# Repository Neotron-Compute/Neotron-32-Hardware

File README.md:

# Neotron 32

## A simple 32K ARM-powered home computer.

The Neotron 32 brings the classic 1980s home-computer design up-to-date. Our tech is based on the tried and true single board ARM computer model offering a hacker friendly platform for your retro project. It aims to bring the retro computing feel, with DOS and BASIC like environments and semi-modern interfaces, like SD cards and SVGA. And all the system software is Open Source and written in the Rust Programming Language, and all the hardware is Open Source too.

With an ARM Cortex-M4 based MCU the Neotron-32 gets you right back into the hardware. With only 32 KiB of RAM, the challenge is to squeeze the maximum out of the minimum amount of resources. We've got 48x36 text mode, 384x288 bitmap mode, 3-channel audio synthesiser, joystick support and FAT filesystem support ... but there's still room for you to squeeze some more out the system.

## Hardware

  - **CPU:** Texas Instruments Tiva-C TM4C123
  - **Processor Core**: 80 MHz ARM Cortex-M4 (approximately 95% CPU taken drawing the screen, leaving a ~ 4 MHz ARM)
  - **RAM:** 32 KiB on-chip SRAM
  - **ROM:** 256 KiB on-chip Flash
  - **GPU:** No GPU - CPU generates 8 colour 400x300 video
  - **GPU RAM:** Shared with main SRAM
  - **Video Output:** VGA (fixed at 800x600 60 Hz)
  - **Storage:** Micro SD Card slot, supports FAT16/FAT32 and MS-DOS partition tables
  - **USB:** 1x USB 2.0 Full-speed OTG micro-AB port (internal - support TBD)
  - **Audio:** 3.5mm Line Out with Mono/Stereo jumper
  - **Keyboard/Mouse:** 2x PS/2 Ports (2x 6-pin mini-DIN)
  - **MIDI**: MIDI In and MIDI Out (2x 5-pin 180-degree DIN)
  - **Serial**: RS-232 on 10-pin 2.54mm header suitable for DE-9 plug on IDC ribbon
  - **Parallel**: 3.3v PC-style Parallel Port on 26-pin 2.54mm header suitable for DB-25 plug on IDC ribbon. Also functions as 3.3v GPIO with 12 outputs and 4 inputs.
  - **Joystick**: 2x 9-pin game ports (supports Atari-compatible two-button joysticks, or SEGA MegaDrive/Genesis controllers)
  - **Expansion**: 2x internal 2.54mm 2x6 headers carrying power, SPI, I2C and a dedicated IRQ line
  - **Wi-Fi**: 2x4 pin socket for ESP-01 Wi-Fi module
  - **RTC**: MCP7940 Real-time clock, with coin-cell battery backup
  - **Mechanical Form Factor:** Fits Hammond [1598C] case

[1598C]: ./datasheets/Hammond%201598C.pdf

## Parts Required

  - **PCBA**: Load the [Neotron-32 schematic](./neotron-32.sch) in Kicad, or see the [Neotron-32 Release Area] on Github for PDFs, Gerbers and a CSV bill-of-materials.
  - **Case**: Hammond [1598C], in your choice of colour. The case will include mounting screws, feet and two un-cut end panels.
  - **End panels**: Cut the panels supplied with the case according to [the drawing](./endpanels/endpanels.dxf). There is a PDF version in the [Neotron-32 Release Area].
  - **SD Card**: Any micro-SD or micro-SDHC card should work. Tested with Sandisk 8GB micro-SDHC cards, formatted with a single FAT32 partition.
  - **Monitor**: You will need monitor with 15-pin VGA input that can handle 800x600 resolution @ 60 Hz. Most higher resolution LCD panels will up-scale the image, but the quality of the scaling may not be ideal. A CRT will give a better image, but you may need to wind up the contrast and brightness to get a workable picture. An old 800x600 native resolution LCD would be ideal.
  - **Power Supply**: You need a standard mobile phone charger or other USB power source, and a standard USB A to B cable (like you would use for a USB printer).
  - **Ribbon cables**: The DB25 Parallel Port and DE9 RS-232 Serial port require a 2.54mm pin header to D-Sub ribbon cable. You can scavenge them from an old PC, or buy them new from Amazon, eBay or AliExpress for a few UK pounds.
  - **Keyboard and Mouse**: Any PS/2 Keyboard and PS/2 Mouse should work. In theory you could also use an RS-232 Serial Mouse but there's no driver support for that.
  - **Tiva-C Launchpad**: Contains the brains of the system. You want the EK-TM4C123GXL - *not* the EK-TM4C129 (which is much larger), or the older LM4F120 Launchpad (which is almost compatible, but audio won't work). You can buy these online at places like [Digikey](https://www.digikey.co.uk/products/en?keywords=296-35760-ND) or [Farnell](https://uk.farnell.com/texas-instruments/ek-tm4c123gxl/launchpad-tiva-c-evaluation-kit/dp/3126091).
  - **Joysticks**: Any Atari-compatible 9-pin digital joystick should work. You can connect up to two at once, for two player gaming. Sega MegaDrive/Genesis controllers should also work (although on the 6-button variant only the main A/B/C/Start buttons will work, not the extra three fire buttons).
  - **Audio**: The audio output is straight from the microcontroller and so is pretty weak. We recommend using amplified speakers, or an external headphone amplifier. Connecting headphones directly is untested and may pull too much current from the microcontroller.
  - **MIDI**: If you want to hook up a MIDI Synthesiser like a Roland MT-32, or a MIDI Keyboard, you just need standard 5-pin DIN MIDI cables. USB MIDI devices are not supported.
  - **USB**: The Tiva-C Launchpad has a USB micro-AB connector into which you can plug a Raspberry Pi Zero compatible micro-A to full-size A adaptor. There is no USB support in firmware yet, and the board can only supply a limited amount of current, so don't expect your mobile phone to charge.
  - **Switches**: You'll need a 250 mA On/Off switch you can fix to the case to power the unit on (or short the header with a jumper), plus a momentary switch to reset the system.

You can find a complete BOM (including the Tiva-C Launchpad and all the connectors, but excluding the PCB, case and Serial/Parallel ribbon cables), on [Octopart]. Gerbers and BOM are also available on [OpenHardware] and [Kitspace]. Don't forget, if you get the Hammond case, you'll need to drill out or mill the endplates yourself to take the connectors.

[Neotron-32 Release Area]: https://github.com/Neotron-Compute/Neotron-32-Hardware/releases
[Octopart]: https://octopart.com/bom-tool/tBdBR3vl
[OpenHardware]: https://www.openhardware.io/view/783/Neotron-32
[Kitspace]: https://kitspace.org/boards/github.com/neotron-compute/neotron-32-hardware/

## Git Setup

We recommend you have the following Git config set:

```console
$ git config --global filter.kicad_project.clean "sed -E 's/^update=.*$/update=Date/'"
$ git config --global filter.kicad_project.smudge cat
$ git config --global filter.kicad_sch.clean "sed -E 's/#(PWR|FLG)[0-9]+/#\1?/'"
$ git config --global filter.kicad_sch.smudge cat
```

See https://jnavila.github.io/plotkicadsch/ for details.

## Software

You will need to flash both the [Neotron 32 BIOS](https://github.com/neotron-compute/Neotron-32-BIOS) and the [Neotron OS](https://github.com/neotron-compute/Neotron-OS). The TM4C123 Launchpad has an on-board USB programming tool, which is supported by OpenOCD, so no extra hardware is required.

Once running the OS, you can load applications from the SD card. Applications can be written in C or in Rust, using the [Neotron SDK](https://github.com/neotron-compute/Neotron-SDK).

## Licence

This schematic and PCB design is Copyright (c) Jonathan 'theJPster' Pallant and other Neotron 32 contributors.

This work is licensed under a [Creative Commons Attribution-ShareAlike 4.0 International License](http://creativecommons.org/licenses/by-sa/4.0/).

## Contribution Agreement

Unless you explicitly state otherwise, any contribution intentionally submitted for inclusion in the work by you, as defined in the Apache-2.0 license, shall be licensed as above, without any additional terms or conditions.

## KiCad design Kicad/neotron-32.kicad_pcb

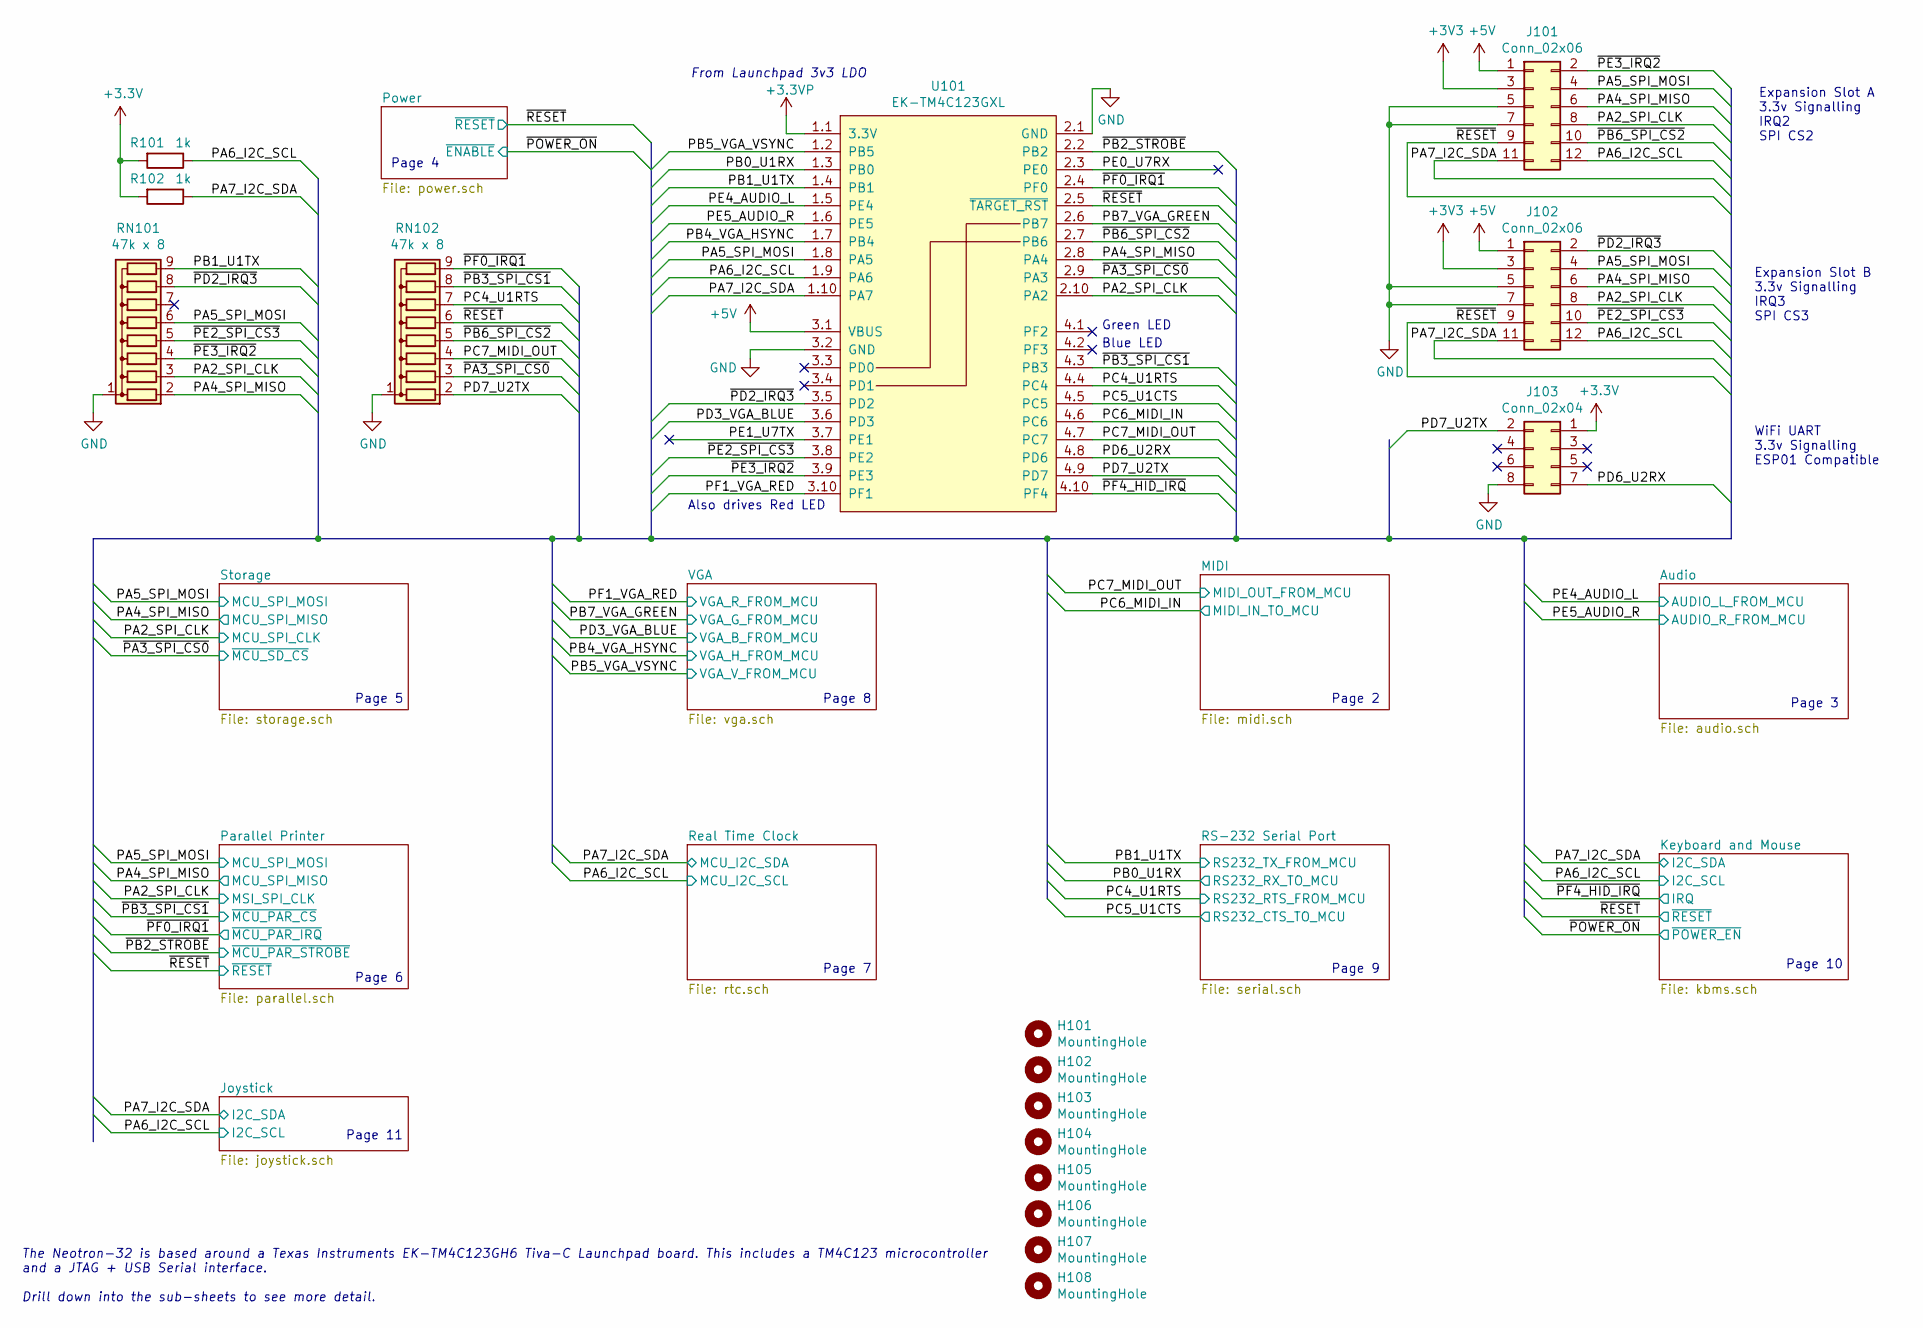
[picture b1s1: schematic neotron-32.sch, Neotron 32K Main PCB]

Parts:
H101, H102, H103, H104, H105, H106, H107, H108: MountingHole; MountingHole_3.5mm_Pad_Via
J101, J102: Conn_02x06; PinHeader_2x06_P2.54mm_Vertical; mpn M20-9760346
J103: Conn_02x04; PinSocket_2x04_P2.54mm_Vertical; mpn RS2-08-G
R101, R102: 1k; R_Axial_DIN0207_L6.3mm_D2.5mm_P10.16mm_Horizontal; mpn CF14JT1K00; digikey# CF14JT1K00CT-ND
RN101, RN102: 47k x 8; R_Array_SIP9; mpn 4609X-101-473LF
U101: EK-TM4C123GXL; Launchpad_4x10; mpn EK-TM4C123GXL;M20-9981046;M20-9981046; digikey# 296-35760-ND

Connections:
+5V: J101.1, J102.1, U101.3.1 (VBUS); also elsewhere on the board
/PA2_SPI_CLK: J101.8, J102.8, RN101.3 (R2), U101.2.10 (PA2); also elsewhere on the board
/PA4_SPI_MISO: J101.6, J102.6, RN101.2 (R1), U101.2.8 (PA4); also elsewhere on the board
/PA5_SPI_MOSI: J101.4, J102.4, RN101.6 (R5), U101.1.8 (PA5); also elsewhere on the board
/PA6_I2C_SCL: J101.12, J102.12, R101.1, U101.1.9 (PA6); also elsewhere on the board
/PA7_I2C_SDA: J101.11, J102.11, R102.1, U101.1.10 (PA7); also elsewhere on the board
/PB0_U1RX: U101.1.3 (PB0); also elsewhere on the board
/PB1_U1TX: RN101.9 (R8), U101.1.4 (PB1); also elsewhere on the board
/PB4_VGA_HSYNC: U101.1.7 (PB4); also elsewhere on the board
/PB5_VGA_VSYNC: U101.1.2 (PB5); also elsewhere on the board
/PB7_VGA_GREEN: U101.2.6 (PB7); also elsewhere on the board
/PC4_U1RTS: RN102.7 (R6), U101.4.4 (PC4); also elsewhere on the board
/PC5_U1CTS: U101.4.5 (PC5); also elsewhere on the board
/PC6_MIDI_IN: U101.4.6 (PC6); also elsewhere on the board
/PC7_MIDI_OUT: RN102.4 (R3), U101.4.7 (PC7); also elsewhere on the board
/PD3_VGA_BLUE: U101.3.6 (PD3); also elsewhere on the board
/PD6_U2RX: J103.7, U101.4.8 (PD6)
/PD7_U2TX: J103.2, RN102.2 (R1), U101.4.9 (PD7)
/PE4_AUDIO_L: U101.1.5 (PE4); also elsewhere on the board
/PE5_AUDIO_R: U101.1.6 (PE5); also elsewhere on the board
/PF1_VGA_RED: U101.3.10 (PF1); also elsewhere on the board
/~PA3_SPI_CS0: RN102.3 (R2), U101.2.9 (PA3); also elsewhere on the board
/~PB2_STROBE: U101.2.2 (PB2); also elsewhere on the board
/~PB3_SPI_CS1: RN102.8 (R7), U101.4.3 (PB3~); also elsewhere on the board
/~PB6_SPI_CS2: J101.10, RN102.5 (R4), U101.2.7 (PB6)
/~PD2_IRQ3: J102.2, RN101.8 (R7), U101.3.5 (PD2)
/~PE2_SPI_CS3: J102.10, RN101.5 (R4), U101.3.8 (PE2)
/~PE3_IRQ2: J101.2, RN101.4 (R3), U101.3.9 (PE3)
/~PF0_IRQ1: RN102.9 (R8), U101.2.4 (PF0); also elsewhere on the board
/~PF4_HID_IRQ: U101.4.10 (PF4); also elsewhere on the board
/~RESET: J101.9, J102.9, RN102.6 (R5), U101.2.5 (~TARGET_RST); also elsewhere on the board
GND: J101.5, J101.7, J102.5, J102.7, J103.8, RN101.1 (common), RN102.1 (common), U101.2.1 (GND), U101.3.2 (GND); also elsewhere on the board

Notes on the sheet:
Green LED
Blue LED
From Launchpad 3v3 LDO
Expansion Slot A 3.3v Signalling IRQ2 SPI CS2
WiFi UART 3.3v Signalling ESP01 Compatible
The Neotron-32 is based around a Texas Instruments EK-TM4C123GH6 Tiva-C Launchpad board. This includes a TM4C123 microcontroller and a JTAG + USB Serial interface. Drill down into the sub-sheets to see more detail.
Page 4
Page 5
Page 6
Page 7
Page 8
Page 2
Page 9
Page 3
Page 10
Expansion Slot B 3.3v Signalling IRQ3 SPI CS3
Also drives Red LED
Page 11

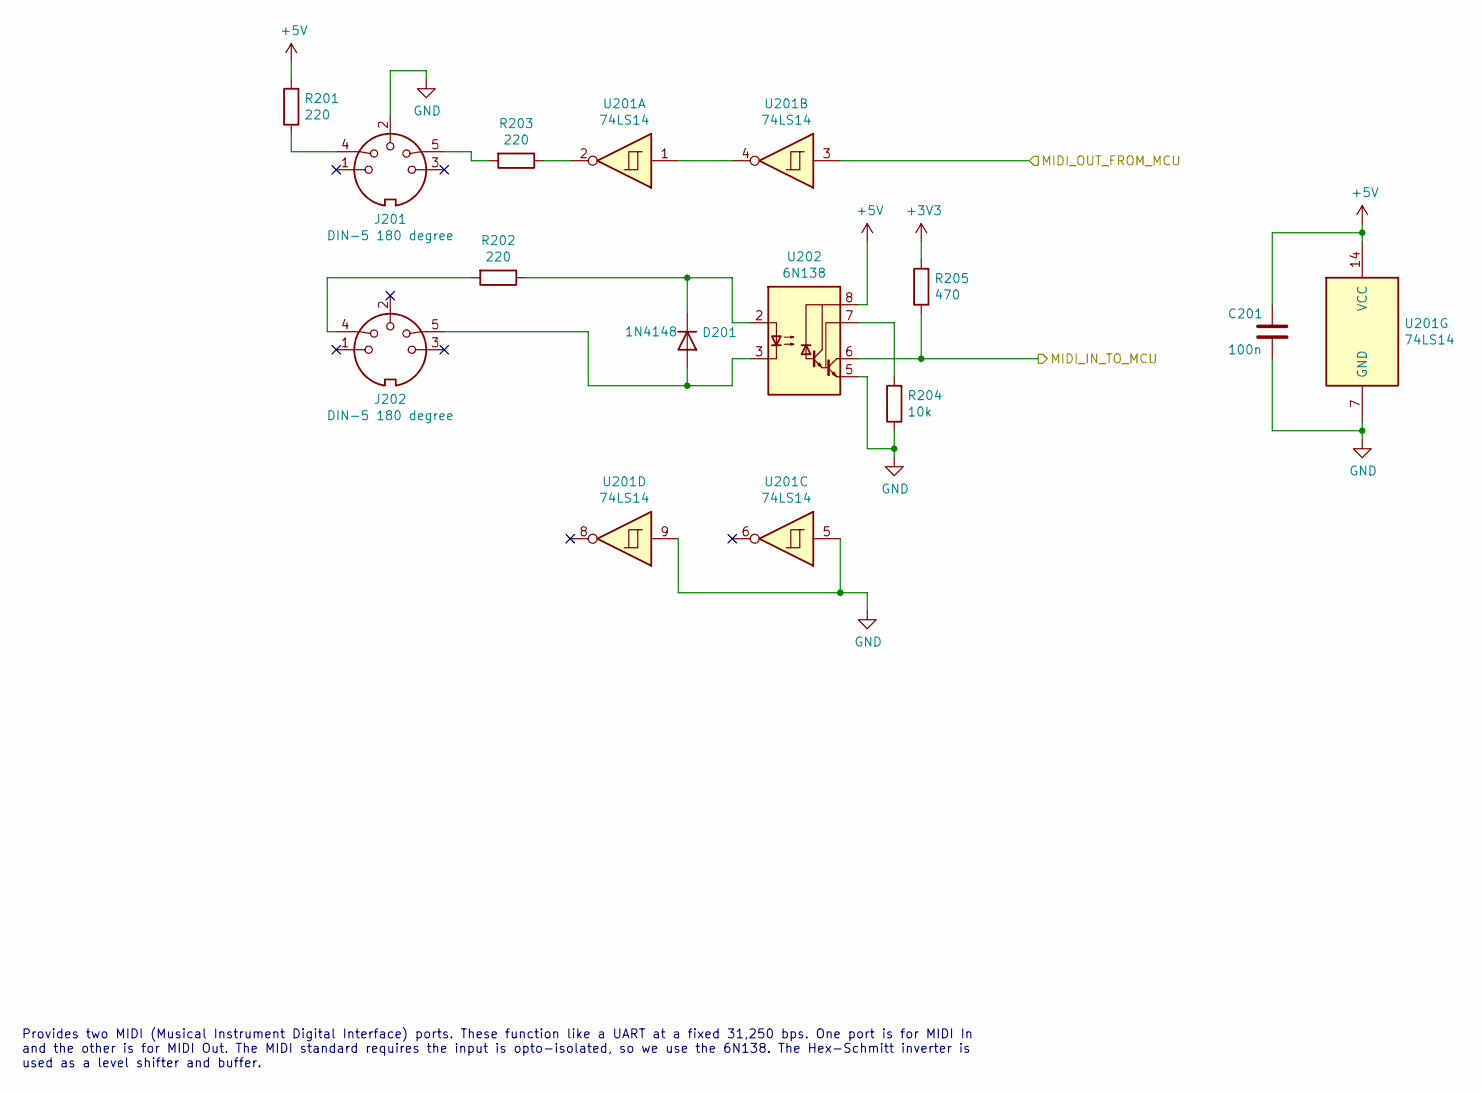
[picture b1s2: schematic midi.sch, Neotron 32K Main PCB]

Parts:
C201: 100n; C_Disc_D3.0mm_W2.0mm_P2.50mm; mpn K104K15X7RF5TL2
D201: 1N4148; D_DO-35_SOD27_P7.62mm_Horizontal; mpn 1N4148TR
J201, J202: DIN-5 180 degree; 5P180_DIN_Socket; mpn 491-087
R201, R202, R203: 220; R_Axial_DIN0207_L6.3mm_D2.5mm_P10.16mm_Horizontal; mpn CF14JT220R; digikey# CF14JT220RCT-ND
R204: 10k; R_Axial_DIN0207_L6.3mm_D2.5mm_P10.16mm_Horizontal; mpn CF14JT10K0; digikey# CF14JT10K0CT-ND
R205: 470; R_Axial_DIN0207_L6.3mm_D2.5mm_P10.16mm_Horizontal; mpn CF14JT470R; digikey# CF14JT470RCT-ND
U201: 74LS14; DIP-14_W7.62mm; mpn SN74LS14N;ED14DT
U202: 6N138; DIP-8_W7.62mm; mpn 6N138;ED08DT

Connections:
+5V: C201.1, R201.2, U201.14 (VCC), U202.8 (VCC); also elsewhere on the board
/PC6_MIDI_IN: R205.1, U202.6 (VO2); also elsewhere on the board
/PC7_MIDI_OUT: U201.3; also elsewhere on the board
GND: C201.2, J201.2, R204.1, U201.5, U201.7 (GND), U201.9, U202.5 (GND); also elsewhere on the board
unnamed: D201.1 (K), R202.1, U202.2 (C1)
unnamed: D201.2 (A), J202.5, U202.3 (C2)
unnamed: J201.4, R201.1
unnamed: J201.5, R203.2
unnamed: J202.4, R202.2
unnamed: R203.1, U201.2
unnamed: R204.2, U202.7 (VO1)
unnamed: U201.1, U201.4

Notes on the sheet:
Provides two MIDI (Musical Instrument Digital Interface) ports. These function like a UART at a fixed 31,250 bps. One port is for MIDI In and the other is for MIDI Out. The MIDI standard requires the input is opto-isolated, so we use the 6N138. The Hex-Schmitt inverter is used as a level shifter an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

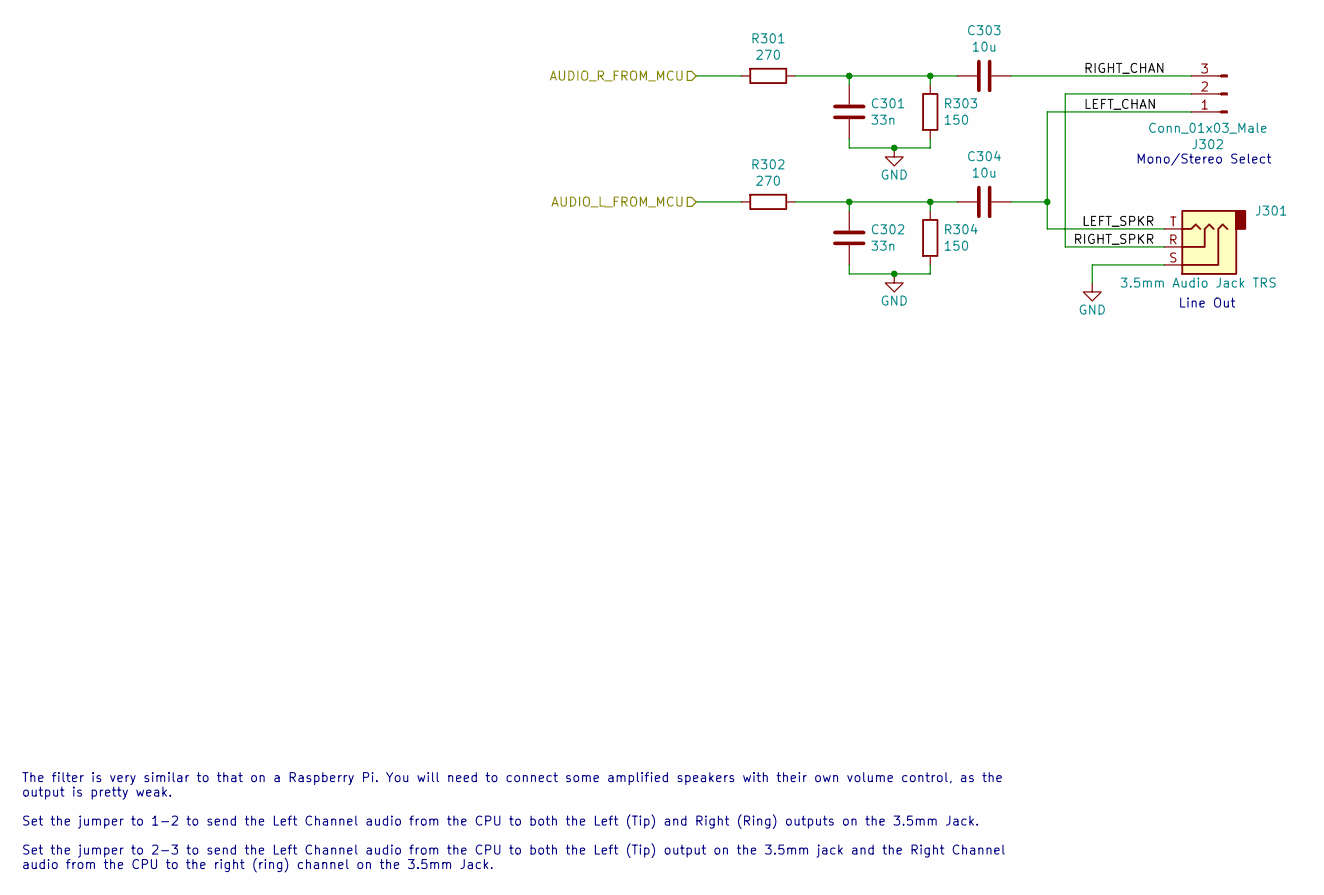
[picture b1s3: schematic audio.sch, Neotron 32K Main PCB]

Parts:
C301, C302: 33n; C_Disc_D3.0mm_W2.0mm_P2.50mm; mpn K333K15X7RF5TL2
C303, C304: 10u; CP_Radial_D6.3mm_P2.50mm; mpn MAL203858109E3
J301: 3.5mm Audio Jack TRS; Jack_3.5mm_CUI_SJ1-3533NG_Horizontal; mpn SJ1-3533NG
J302: Conn_01x03_Male; PinHeader_1x03_P2.54mm_Vertical
R301, R302: 270; R_Axial_DIN0207_L6.3mm_D2.5mm_P10.16mm_Horizontal; mpn CF14JT270R; digikey# CF14JT270RCT-ND
R303, R304: 150; R_Axial_DIN0207_L6.3mm_D2.5mm_P10.16mm_Horizontal; mpn CF14JT150R; digikey# CF14JT150RCT-ND

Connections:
/Audio/LEFT_CHAN: C304.2, J301.T, J302.1
/Audio/RIGHT_CHAN: C303.2, J302.3
/Audio/RIGHT_SPKR: J301.R, J302.2
/PE4_AUDIO_L: R302.2; also elsewhere on the board
/PE5_AUDIO_R: R301.2; also elsewhere on the board
GND: C301.1, C302.1, J301.S, R303.2, R304.2; also elsewhere on the board
unnamed: C301.2, C303.1, R301.1, R303.1
unnamed: C302.2, C304.1, R302.1, R304.1

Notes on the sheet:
Mono/Stereo Select
Line Out
The filter is very similar to that on a Raspberry Pi. You will need to connect some amplified speakers with their own volume control, as the output is pretty weak. Set the jumper to 1-2 to send the Left Channel audio from the CPU to both the Left (Tip) and Right (Ring) outputs on the 3.5mm Jack. Se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

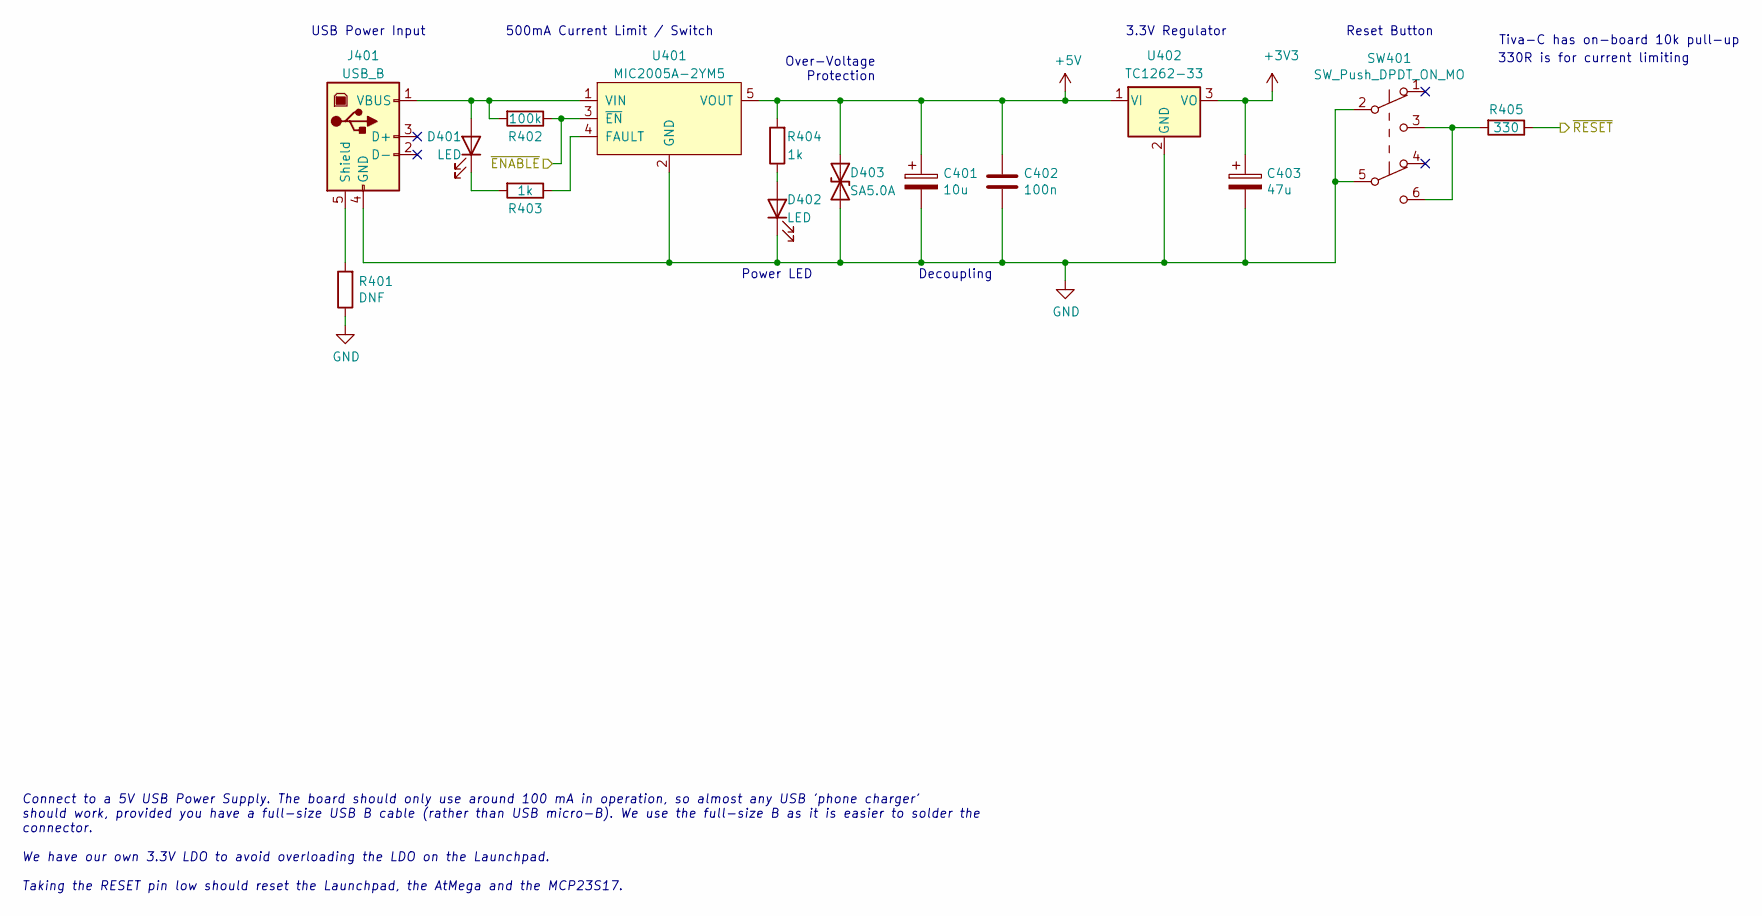
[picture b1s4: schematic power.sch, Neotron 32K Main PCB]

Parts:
C401: 10u; CP_Radial_D6.3mm_P2.50mm; mpn MAL203858109E3
C402: 100n; C_Disc_D3.0mm_W2.0mm_P2.50mm; mpn K104K15X7RF5TL2
C403: 47u; CP_Radial_D6.3mm_P2.50mm; mpn MAL214250479E3
D401, D402: LED; LED_D3.0mm
D403: SA5.0A; D_DO-15_P12.70mm_Horizontal; mpn SA5.0A
J401: USB_B; USB_B_OST_USB-B1HSxx_Horizontal; mpn USB-B1HSB6
R401: DNF; R_Axial_DIN0207_L6.3mm_D2.5mm_P10.16mm_Horizontal
R402: 100k; R_Axial_DIN0207_L6.3mm_D2.5mm_P10.16mm_Horizontal
R403, R404: 1k; R_Axial_DIN0207_L6.3mm_D2.5mm_P10.16mm_Horizontal
R405: 330; R_Axial_DIN0207_L6.3mm_D2.5mm_P10.16mm_Horizontal; mpn CF14JT330R; digikey# CF14JT330RCT-ND
SW401: SW_Push_DPDT_ON_MO; PHB2UEETS1A; mpn PHB2UOATS1A
U401: MIC2005A-2YM5; SOT-23-5_HandSoldering
U402: TC1262-33; TO-220-3_Vertical; mpn TC1262-3.3VAB

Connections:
+5V: C401.1, C402.1, D403.1 (A1), R404.2, U401.5 (VOUT), U402.1 (VI); also elsewhere on the board
/~POWER_ON: R402.1, U401.3 (~EN); also elsewhere on the board
/~RESET: R405.1; also elsewhere on the board
GND: C401.2, C402.2, C403.2, D402.1 (K), D403.2 (A2), J401.4 (GND), R401.1, SW401.2 (B), SW401.5 (B), U401.2 (GND), U402.2 (GND); also elsewhere on the board
unnamed: D401.1 (K), R403.2
unnamed: D401.2 (A), J401.1 (VBUS), R402.2, U401.1 (VIN)
unnamed: D402.2 (A), R404.1
unnamed: J401.5 (Shield), R401.2
unnamed: R403.1, U401.4 (FAULT)
unnamed: R405.2, SW401.3 (C), SW401.6 (C)

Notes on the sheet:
Reset Button
500mA Current Limit / Switch
USB Power Input
3.3V Regulator
Tiva-C has on-board 10k pull-up
330R is for current limiting
Connect to a 5V USB Power Supply. The board should only use around 100 mA in operation, so almost any USB 'phone charger' should work, provided you have a full-size USB B cable (rather than USB micro-B). We use the full-size B as it is easier to solder the connector. We have our own 3.3V LDO to avo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
Power LED
Over-Voltage Protection
Decoupling

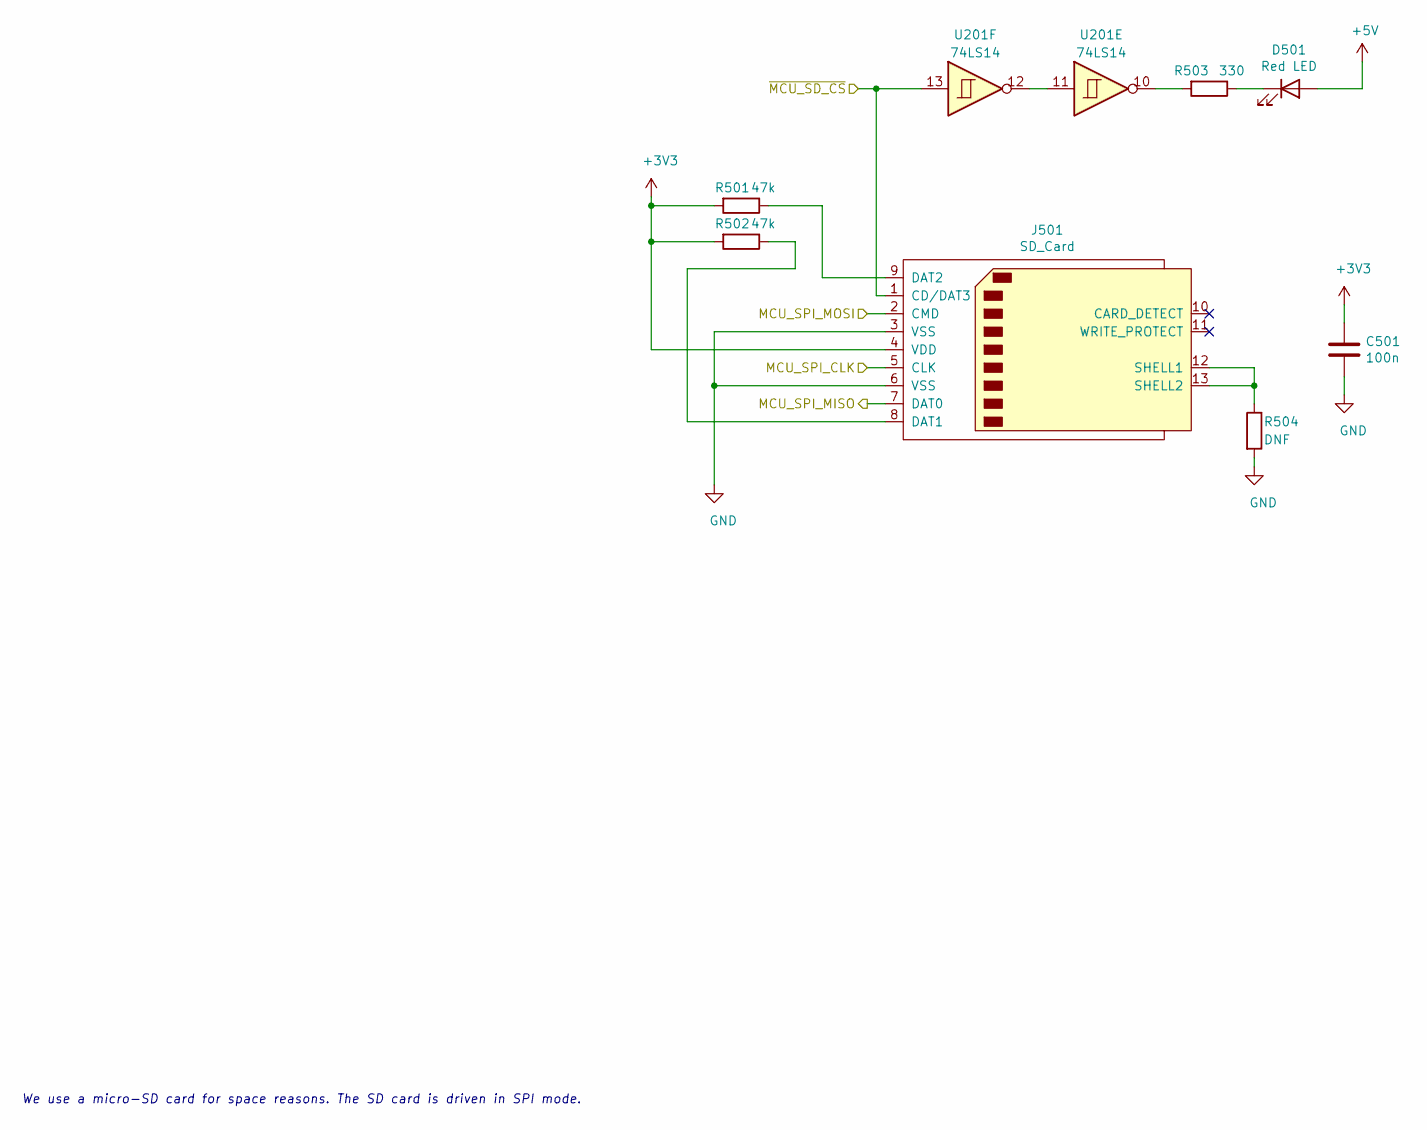
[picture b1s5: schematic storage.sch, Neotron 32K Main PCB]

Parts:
C501: 100n; C_Disc_D3.0mm_W2.0mm_P2.50mm; mpn K104K15X7RF5TL2
D501: Red LED; LED_D3.0mm; mpn 151031SS04000
J501: SD_Card; SD_Kyocera_145638109511859+
R501, R502: 47k; R_Axial_DIN0207_L6.3mm_D2.5mm_P10.16mm_Horizontal; mpn CF14JT47K0; digikey# CF14JT47K0CT-ND
R503: 330; R_Axial_DIN0207_L6.3mm_D2.5mm_P10.16mm_Horizontal; mpn CF14JT330R; digikey# CF14JT330RCT-ND
R504: DNF; R_Axial_DIN0207_L6.3mm_D2.5mm_P10.16mm_Horizontal
U201: 74LS14; DIP-14_W7.62mm; mpn SN74LS14N;ED14DT

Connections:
+5V: D501.2 (A); also elsewhere on the board
/PA2_SPI_CLK: J501.5 (CLK); also elsewhere on the board
/PA4_SPI_MISO: J501.7 (DAT0); also elsewhere on the board
/PA5_SPI_MOSI: J501.2 (CMD); also elsewhere on the board
/~PA3_SPI_CS0: J501.1 (CD/DAT3), U201.13; also elsewhere on the board
GND: C501.2, J501.3 (VSS), J501.6 (VSS), R504.2; also elsewhere on the board
unnamed: D501.1 (K), R503.1
unnamed: J501.8 (DAT1), R502.1
unnamed: J501.9 (DAT2), R501.1
unnamed: J501.12 (SHELL1), J501.13 (SHELL2), R504.1
unnamed: R503.2, U201.10
unnamed: U201.11, U201.12

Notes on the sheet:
We use a micro-SD card for space reasons. The SD card is driven in SPI mode.

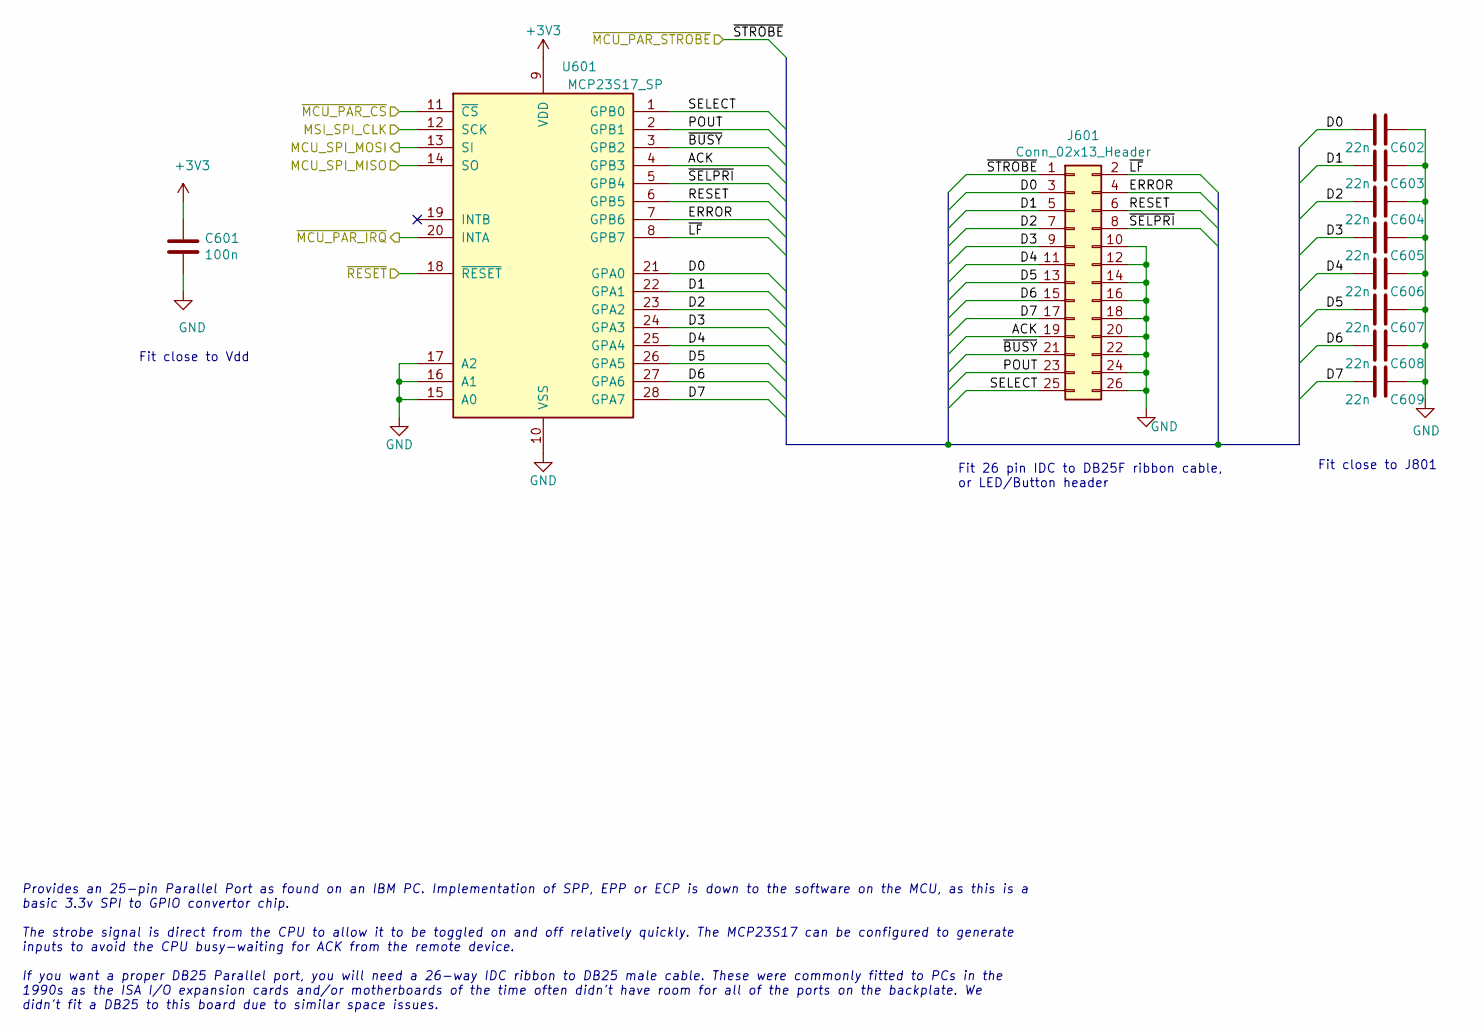
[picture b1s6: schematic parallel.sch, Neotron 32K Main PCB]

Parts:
C601: 100n; C_Disc_D3.0mm_W2.0mm_P2.50mm; mpn K104K15X7RF5TL2
C602, C603, C604, C605, C606, C607, C608, C609: 22n; C_Disc_D3.0mm_W2.0mm_P2.50mm; mpn K223K15X7RF5TL2
J601: Conn_02x13_Header; IDC-Header_2x13_P2.54mm_Vertical; mpn 302-S261
U601: MCP23S17_SP; DIP-28_W7.62mm; mpn MCP23S17-E/SP;ED281DT

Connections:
/PA2_SPI_CLK: U601.12 (SCK); also elsewhere on the board
/PA4_SPI_MISO: U601.14 (SO); also elsewhere on the board
/PA5_SPI_MOSI: U601.13 (SI); also elsewhere on the board
/Parallel Printer/ACK: J601.19, U601.4 (GPB3)
/Parallel Printer/D0: C602.2, J601.3, U601.21 (GPA0)
/Parallel Printer/D1: C603.2, J601.5, U601.22 (GPA1)
/Parallel Printer/D2: C604.2, J601.7, U601.23 (GPA2)
/Parallel Printer/D3: C605.2, J601.9, U601.24 (GPA3)
/Parallel Printer/D4: C606.2, J601.11, U601.25 (GPA4)
/Parallel Printer/D5: C607.2, J601.13, U601.26 (GPA5)
/Parallel Printer/D6: C608.2, J601.15, U601.27 (GPA6)
/Parallel Printer/D7: C609.2, J601.17, U601.28 (GPA7)
/Parallel Printer/ERROR: J601.4, U601.7 (GPB6)
/Parallel Printer/POUT: J601.23, U601.2 (GPB1)
/Parallel Printer/RESET: J601.6, U601.6 (GPB5)
/Parallel Printer/SELECT: J601.25, U601.1 (GPB0)
/Parallel Printer/~BUSY: J601.21, U601.3 (GPB2)
/Parallel Printer/~LF: J601.2, U601.8 (GPB7)
/Parallel Printer/~SELPRI: J601.8, U601.5 (GPB4)
/~PB2_STROBE: J601.1; also elsewhere on the board
/~PB3_SPI_CS1: U601.11 (~CS~); also elsewhere on the board
/~PF0_IRQ1: U601.20 (INTA); also elsewhere on the board
/~RESET: U601.18 (~RESET~); also elsewhere on the board
GND: C601.2, C602.1, C603.1, C604.1, C605.1, C606.1, C607.1, C608.1, C609.1, J601.10, J601.12, J601.14, J601.16, J601.18, J601.20, J601.22, J601.24, J601.26, U601.10 (VSS), U601.15 (A0), U601.16 (A1), U601.17 (A2); also elsewhere on the board

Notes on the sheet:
Fit 26 pin IDC to DB25F ribbon cable, or LED/Button header
Fit close to J801
Fit close to Vdd
Provides an 25-pin Parallel Port as found on an IBM PC. Implementation of SPP, EPP or ECP is down to the software on the MCU, as this is a basic 3.3v SPI to GPIO convertor chip. The strobe signal is direct from the CPU to allow it to be toggled on and off relatively quickly. The MCP23S17 can be con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

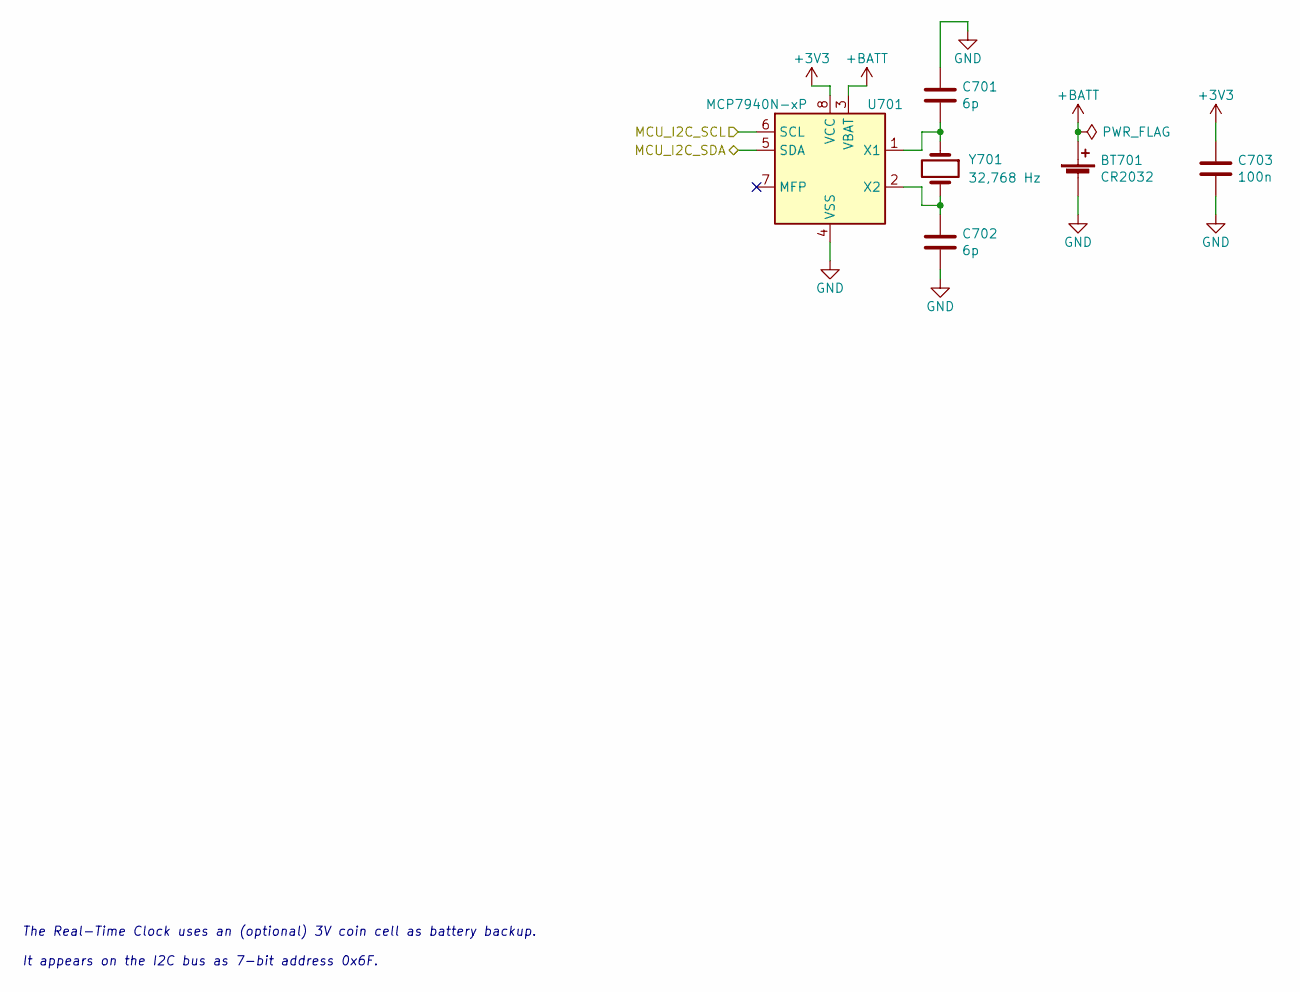
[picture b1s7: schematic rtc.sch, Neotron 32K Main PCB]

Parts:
BT701: CR2032; BatteryHolder_Keystone_103_1x20mm; mpn 103;CR2032
C701, C702: 6p; C_Disc_D3.0mm_W2.0mm_P2.50mm; mpn FG18C0G1H060DNT06
C703: 100n; C_Disc_D3.0mm_W2.0mm_P2.50mm; mpn K104K15X7RF5TL2
U701: MCP7940N-xP; DIP-8_W7.62mm; mpn MCP7940N-I/P;ED08DT
Y701: 32,768 Hz; Crystal_C26-LF_D2.1mm_L6.5mm_Horizontal; mpn CFS-20632768DZBB

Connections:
+BATT: BT701.1 (+), U701.3 (VBAT)
/PA6_I2C_SCL: U701.6 (SCL); also elsewhere on the board
/PA7_I2C_SDA: U701.5 (SDA); also elsewhere on the board
GND: BT701.2 (-), C701.1, C702.2, C703.2, U701.4 (VSS); also elsewhere on the board
unnamed: C701.2, U701.1 (X1), Y701.1
unnamed: C702.1, U701.2 (X2), Y701.2

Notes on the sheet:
The Real-Time Clock uses an (optional) 3V coin cell as battery backup. It appears on the I2C bus as 7-bit address 0x6F.

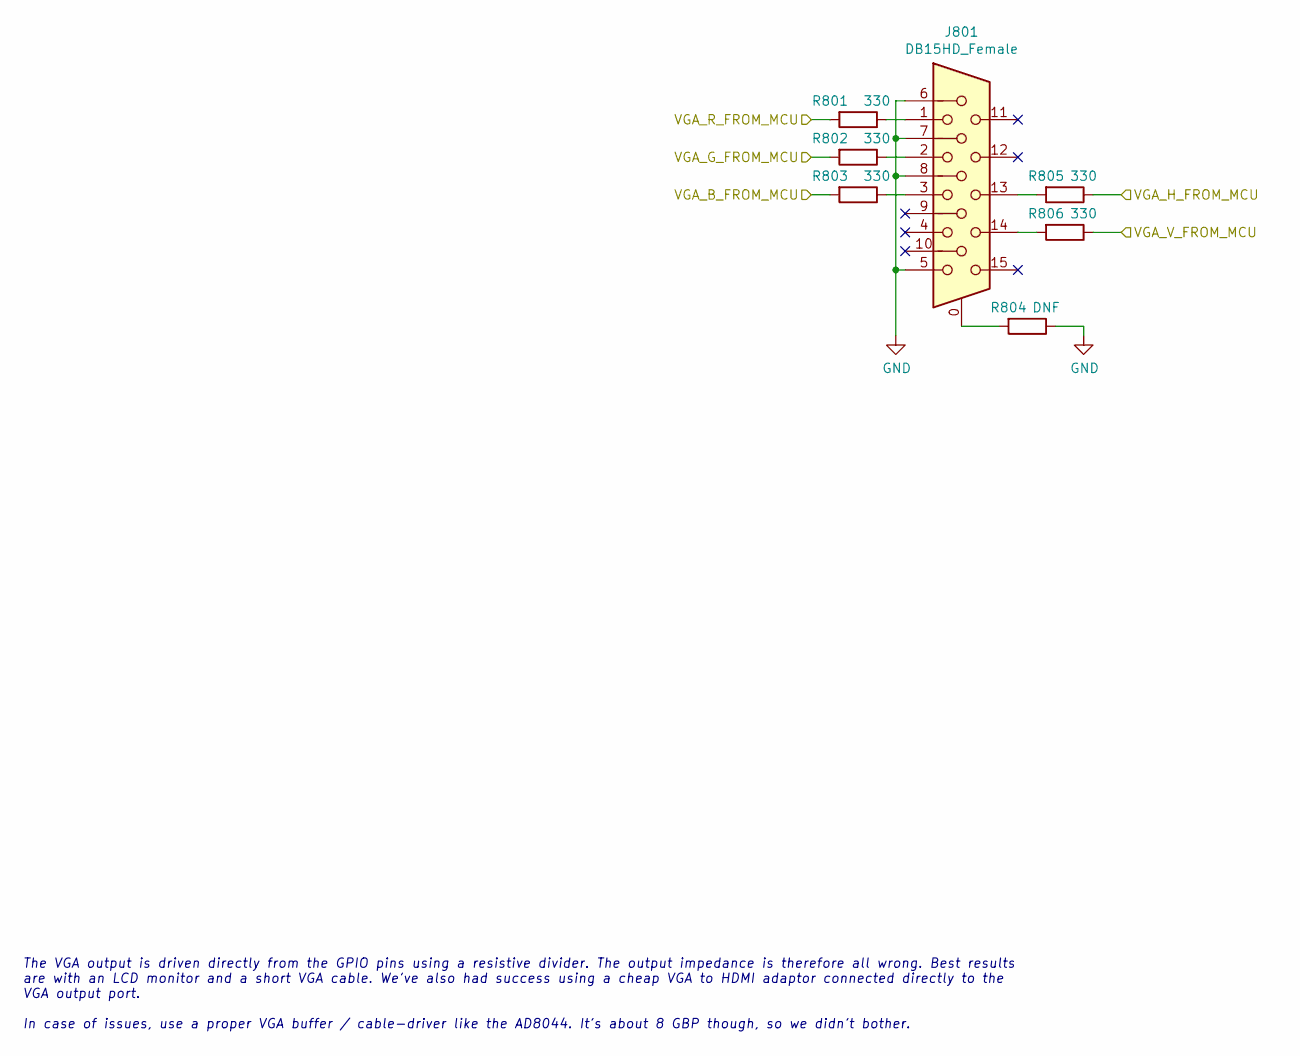
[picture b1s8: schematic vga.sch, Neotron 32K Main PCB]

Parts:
J801: DB15HD_Female; DSUB-15-HD_Female_Horizontal_P2.29x1.98mm_EdgePinOffset3.03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; mpn ICD15S13E4GV00LF
R801, R802, R803: 330; R_Axial_DIN0207_L6.3mm_D2.5mm_P10.16mm_Horizontal; mpn CF14JT330R; digikey# CF14JT330RCT-ND
R804: DNF; R_Axial_DIN0207_L6.3mm_D2.5mm_P10.16mm_Horizontal
R805, R806: 330; R_Axial_DIN0207_L6.3mm_D2.5mm_P10.16mm_Horizontal; mpn CF14JT470R; digikey# CF14JT470RCT-ND

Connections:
/PB4_VGA_HSYNC: R805.1; also elsewhere on the board
/PB5_VGA_VSYNC: R806.1; also elsewhere on the board
/PB7_VGA_GREEN: R802.2; also elsewhere on the board
/PD3_VGA_BLUE: R803.2; also elsewhere on the board
/PF1_VGA_RED: R801.2; also elsewhere on the board
GND: J801.5, J801.6, J801.7, J801.8, R804.1; also elsewhere on the board
unnamed: J801.0, R804.2
unnamed: J801.1, R801.1
unnamed: J801.2, R802.1
unnamed: J801.3, R803.1
unnamed: J801.13, R805.2
unnamed: J801.14, R806.2

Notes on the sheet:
The VGA output is driven directly from the GPIO pins using a resistive divider. The output impedance is therefore all wrong. Best results are with an LCD monitor and a short VGA cable. We've also had success using a cheap VGA to HDMI adaptor connected directly to the VGA output port. In case of iss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
